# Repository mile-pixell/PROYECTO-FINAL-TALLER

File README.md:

# PROYECTO-FINAL-TALLER
En este repo esta el proyecto final de taller de la eetp

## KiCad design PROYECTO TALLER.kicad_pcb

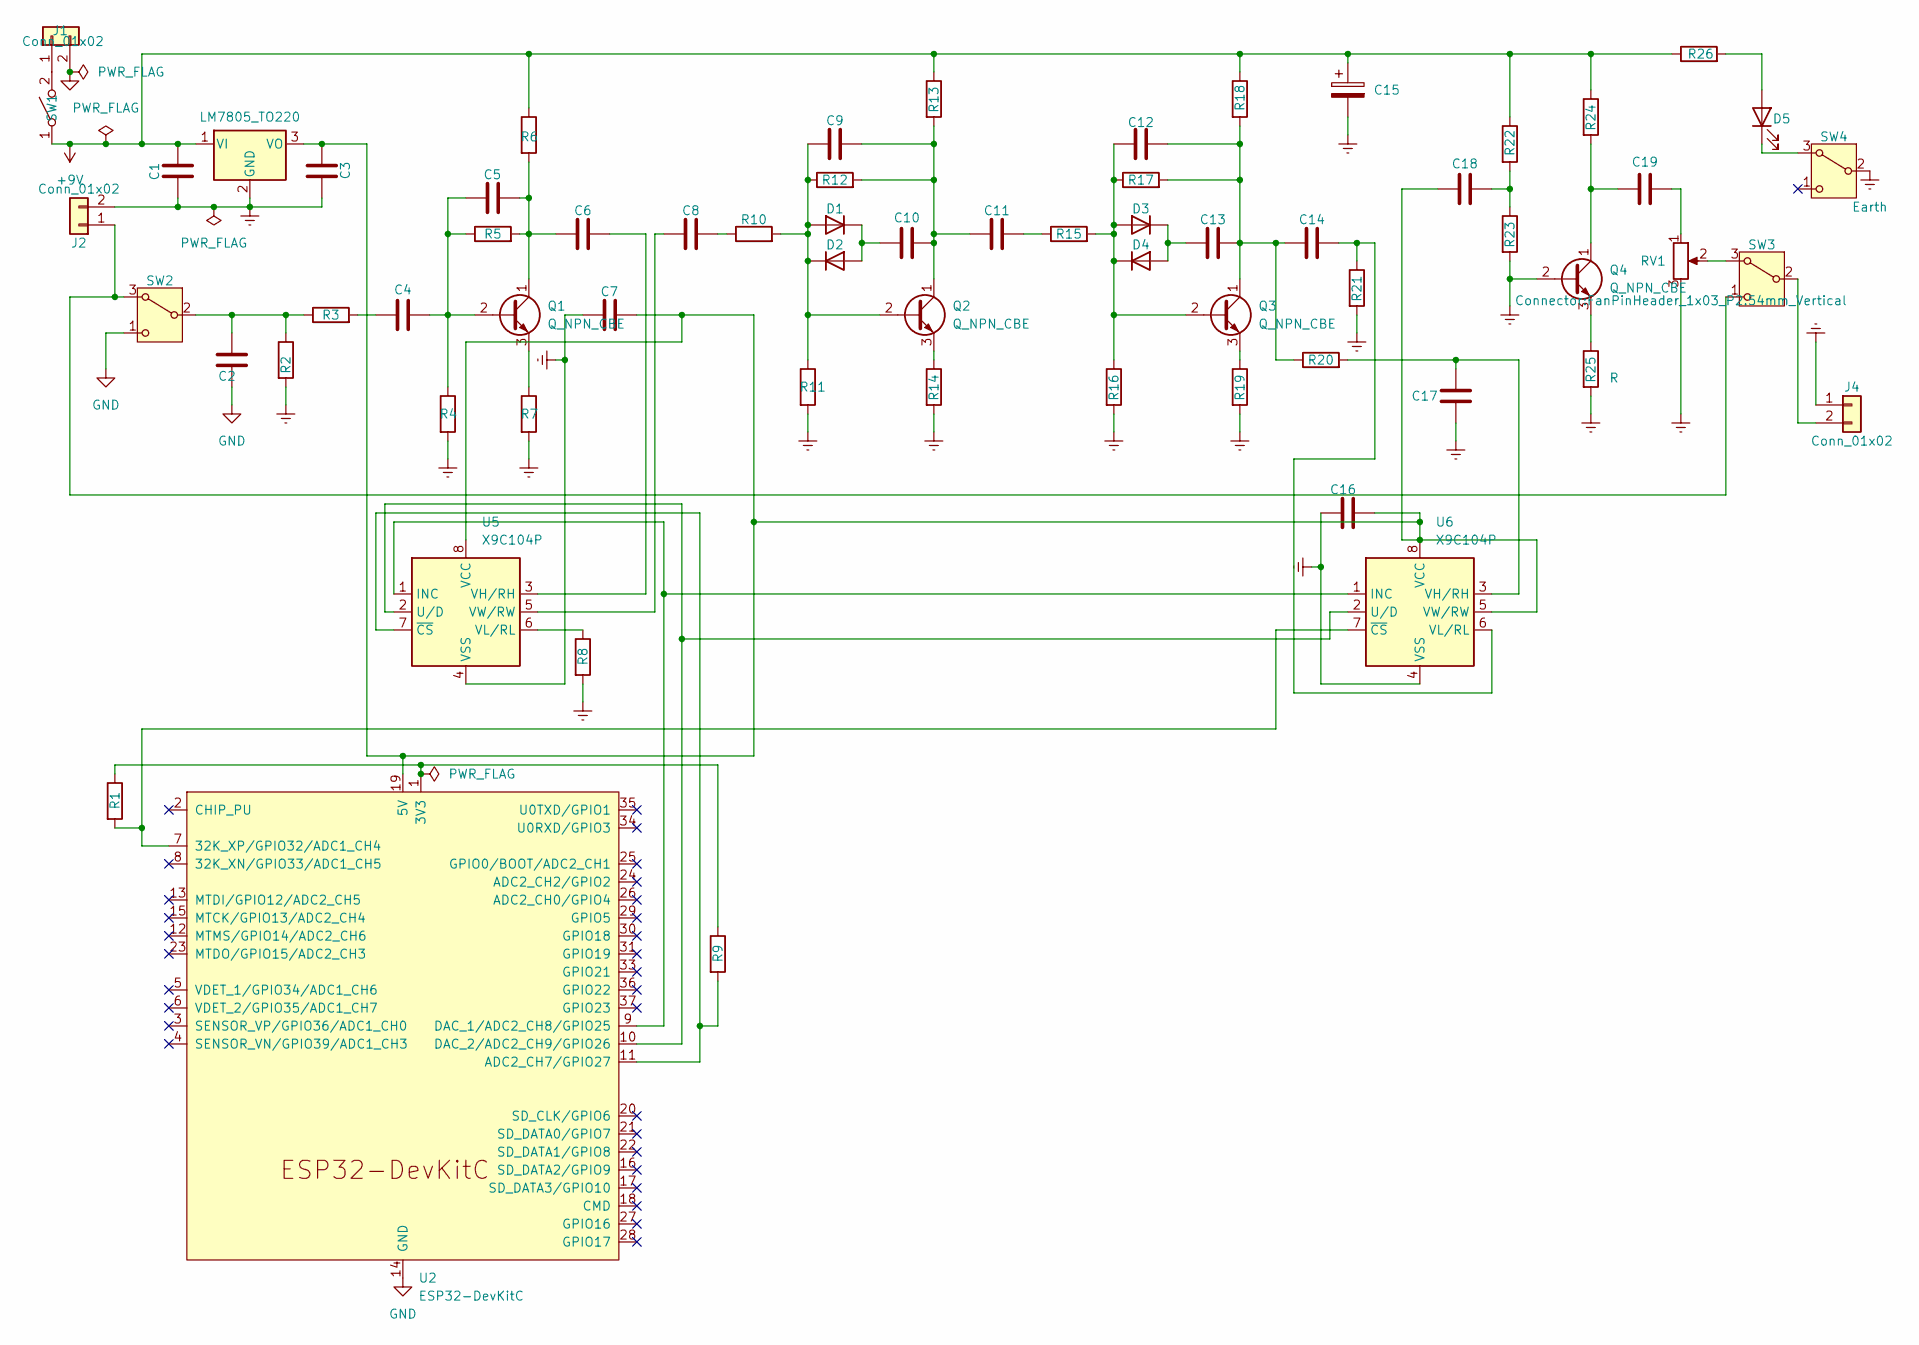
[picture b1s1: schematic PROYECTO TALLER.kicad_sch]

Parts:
C1, C3: C; CP_Radial_D5.0mm_P2.00mm
C2, C4, C5, C6, C7, C8, C9, C10, C11, C12, C13, C14, C16, C17, C18, C19: C; C_Disc_D5.0mm_W2.5mm_P5.00mm
C15: C_Polarized; CP_Radial_D6.3mm_P2.50mm
D1, D2, D3, D4: D; D_DO-35_SOD27_P7.62mm_Horizontal
D5: LED; LED_D5.0mm
J1, J2, J4: Conn_01x02; PinHeader_1x02_P2.54mm_Vertical
Q1, Q2, Q3, Q4: Q_NPN_CBE; TO-92_Inline
R1, R2, R3, R4, R5, R6, R7, R8, R9, R10, R11, R12, R13, R14, R15, R16, R17, R18, R19, R20, R21, R22, R23, R24, R25, R26: R; R_Axial_DIN0207_L6.3mm_D2.5mm_P7.62mm_Horizontal
RV1: FanPinHeader_1x03_P2.54mm_Vertical
SW1: SW_SPST; FanPinHeader_1x03_P2.54mm_Vertical
SW2, SW3, SW4: SW_Nidec_CAS-120A1; FanPinHeader_1x03_P2.54mm_Vertical
U1: LM7805_TO220; TO-220-3_Vertical
U2: ESP32-DevKitC
U5, U6: X9C104P; DIP-8_W7.62mm

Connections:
+9V: C1.2, C15.1, R6.1, R13.1, R18.1, R22.1, R24.1, R26.1, SW1.1 (A), U1.1 (VI)
Earth: C1.1, C3.2, C7.1, C15.2, C16.1, C17.2, J2.2, J4.1, Q4.2 (B), R2.2, R4.2, R7.2, R8.2, R11.2, R14.2, R16.2, R19.2, R21.2, R23.2, R25.2, RV1.3, SW4.2 (B), U1.2 (GND), U5.4 (VSS), U6.4 (VSS)
GND: C2.2, J1.2, SW2.1 (C), U2.14 (GND), U2.32 (GND), U2.38 (GND)
unnamed: C4.1, R3.2
unnamed: C8.2, R10.1
unnamed: C11.2, R15.1
unnamed: C18.2, R22.2, R23.1
unnamed: C19.2, RV1.1
unnamed: C9.1, D1.2 (A), D2.1 (K), Q2.2 (B), R10.2, R11.1, R12.1
unnamed: C10.1, D1.1 (K), D2.2 (A)
unnamed: C12.1, D3.2 (A), D4.1 (K), Q3.2 (B), R15.2, R16.1, R17.1
unnamed: C13.1, D3.1 (K), D4.2 (A)
unnamed: D5.2 (A), R26.2
unnamed: D5.1 (K), SW4.3 (A)
unnamed: J1.1, SW1.2 (B)
unnamed: J2.1, SW2.3 (A), SW3.1 (C)
unnamed: J4.2, SW3.2 (B)
unnamed: C4.2, C5.1, Q1.2 (B), R4.1, R5.1
unnamed: C5.2, C6.1, Q1.1 (C), R5.2, R6.2
unnamed: Q1.3 (E), R7.1
unnamed: C9.2, C10.2, C11.1, Q2.1 (C), R12.2, R13.2
unnamed: Q2.3 (E), R14.1
unnamed: C12.2, C13.2, C14.1, Q3.1 (C), R17.2, R18.2, R20.1
unnamed: Q3.3 (E), R19.1
unnamed: C19.1, Q4.1 (C), R24.2
unnamed: Q4.3 (E), R25.1
unnamed: C2.1, R2.1, R3.1, SW2.2 (B)
unnamed: RV1.2, SW3.3 (A)
unnamed: C3.1, C7.2, C16.2, C18.1, U1.3 (VO), U2.19 (5V), U5.8 (VCC), U6.5 (VW/RW), U6.8 (VCC)
unnamed: R1.1, R9.1, U2.1 (3V3)
unnamed: R1.2, U2.7 (32K_XP/GPIO32/ADC1_CH4), U6.7 (~CS)
unnamed: R9.2, U2.11 (ADC2_CH7/GPIO27), U5.7 (~CS)
unnamed: U2.9 (DAC_1/ADC2_CH8/GPIO25), U5.1 (INC), U6.1 (INC)
unnamed: U2.10 (DAC_2/ADC2_CH9/GPIO26), U5.2 (U/D), U6.2 (U/D)
unnamed: C6.2, U5.3 (VH/RH)
unnamed: R8.1, U5.6 (VL/RL)
unnamed: C8.1, U5.5 (VW/RW)
unnamed: C17.1, R20.2, U6.3 (VH/RH)
unnamed: C14.2, R21.1, U6.6 (VL/RL)

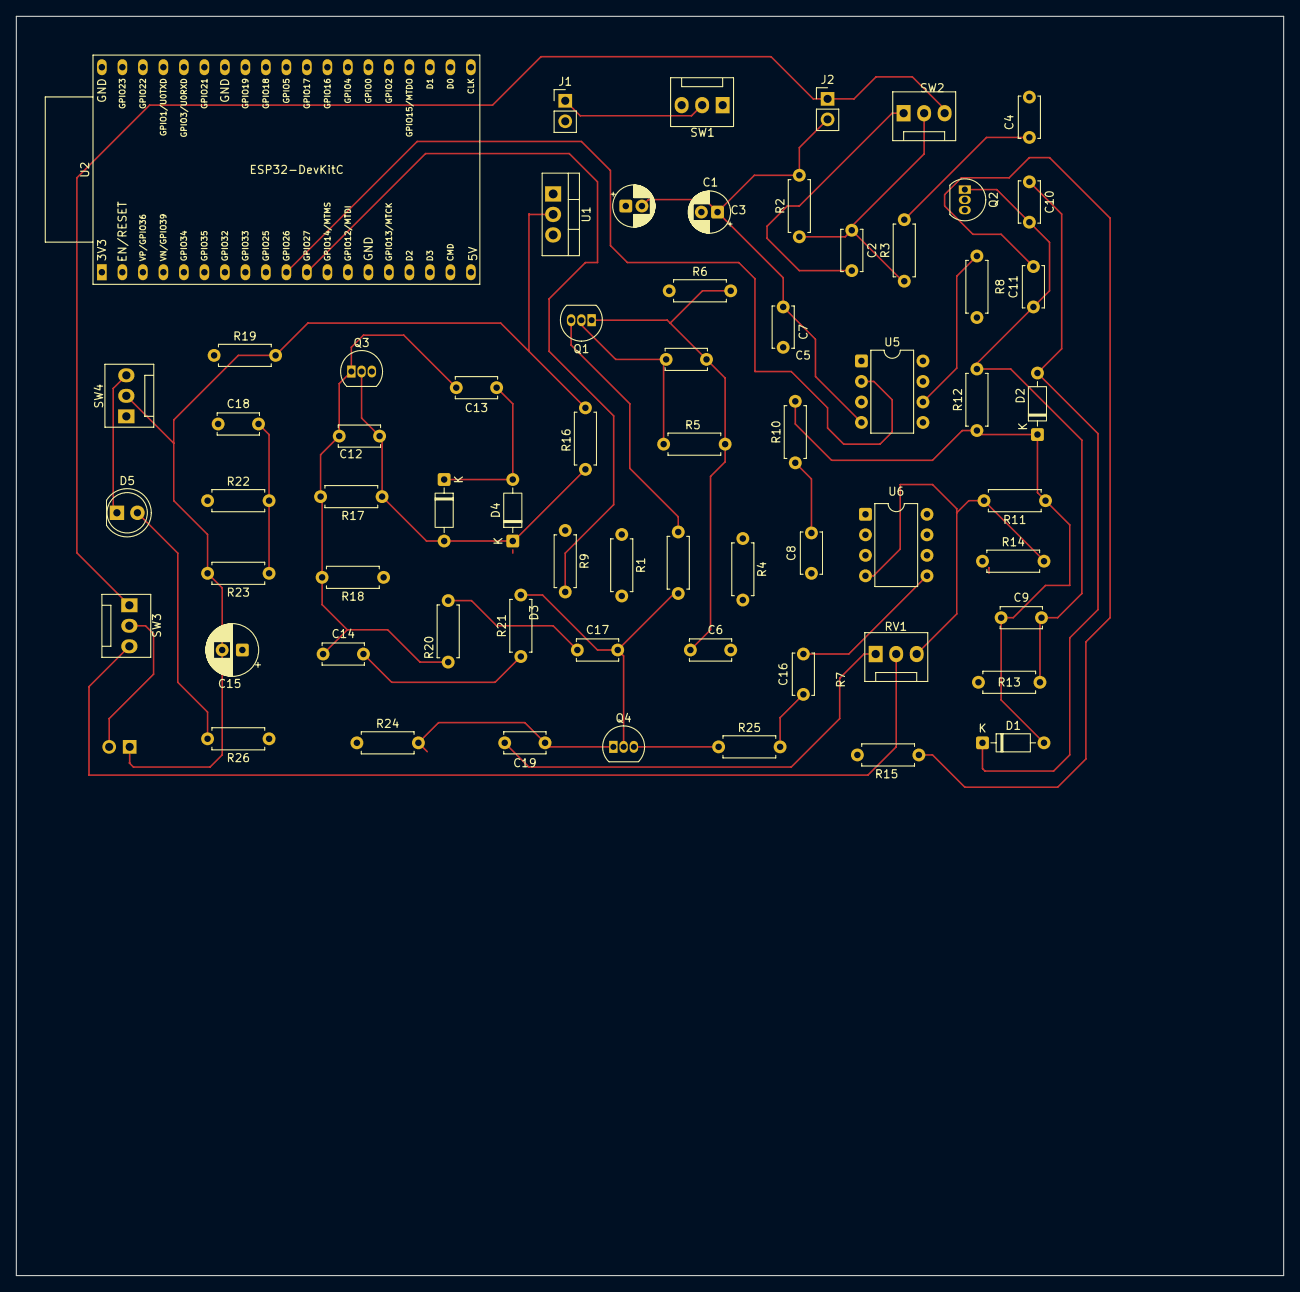
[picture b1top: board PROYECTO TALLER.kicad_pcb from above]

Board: 2 copper layers, 157.0 x 156.0 mm, 66 parts (1 on the bottom side), 39 nets.
